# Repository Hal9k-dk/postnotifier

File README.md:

# postnotifier

Firmware til esp-01 modul samt pcb filer som er brugt til at lave postkasse overvågning i hal9k, så når der kommer post, kommer der automatisk en besked på vores chat tjeneste slack, ved brug af slack api.

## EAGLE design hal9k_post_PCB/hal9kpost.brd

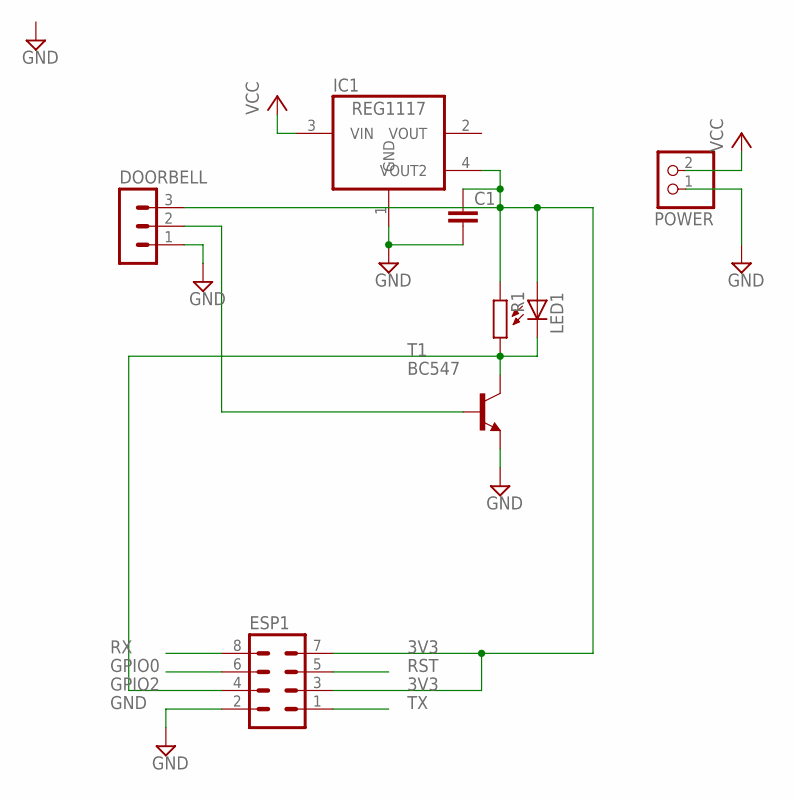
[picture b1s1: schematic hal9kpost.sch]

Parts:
C1: C-EUC0805K; C0805K
DOORBELL: MA03-1
ESP1: MA04-2
IC1: REG1117; SOT223
LED1: LED5MM
POWER: PINHD-1X2; 1X02
R1: R-EU_0207/10; 0207/10
T1: BC547; TO92

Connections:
3V3: C1.1, DOORBELL.3, ESP1.3, ESP1.7, IC1.4 (VOUT2), LED1.A, R1.1
GND: C1.2, DOORBELL.1, ESP1.2, IC1.1 (GND), POWER.1, T1.1 (E)
GPIO0: ESP1.6
GPIO2: ESP1.4, LED1.K (C), R1.2, T1.3 (C)
unnamed: DOORBELL.2, T1.2 (B)
RST: ESP1.5
RX: ESP1.8
TX: ESP1.1
VCC: IC1.3 (VIN), POWER.2

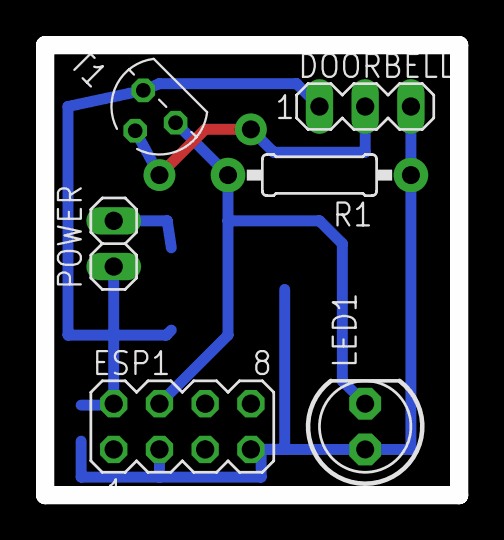
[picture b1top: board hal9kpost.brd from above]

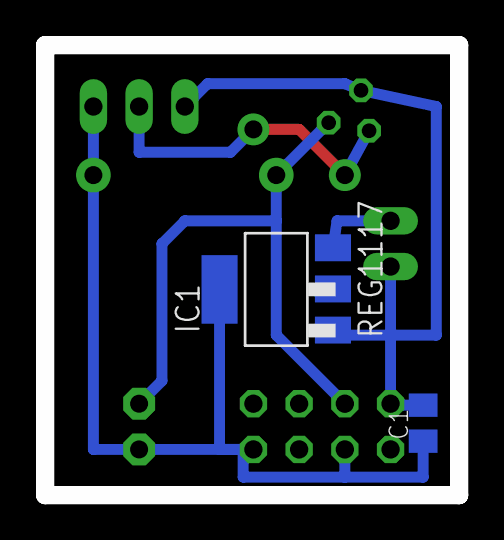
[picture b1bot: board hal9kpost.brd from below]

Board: 2 copper layers, 23.0 x 25.0 mm, 8 parts (2 on the bottom side), 5 nets.

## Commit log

2015-11-21 pcb filer
2015-11-24 Firmware first commit
